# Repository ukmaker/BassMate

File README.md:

# BassMate

This is a simple drum machine and sequencer.

I want to be able to quickly create simple rhythm sequences to help me pratice electric bass, and was looking for something between a basic metronome and a full-fledged DAW.
The Drumbit online app (https://drumbit.app/) is pretty good, but having to point and click while playing an instrument is not tactile enough for me.
Accordingly, BassedMate (https://github.com/ukmaker/BassedMate) was born. This was the first iteration of the project, using a Teensy.

BassMate (this repo) is an evolution. I wanted to eliminate the VS1053 chip and I found the Electrosmith Daisy Seed (https://www.electro-smith.com/daisy/daisy)
which looked like it could do all the synthesis itself. I also found the MusicBoard project (https://github.com/julbouln/musicboard) which inspired me
to try to port to the Seed. This proved to be tricky, so I gave up (I'll try again one day!) and took a different path.

The UI of BassedMate felt a bit off, and when I came across the NavKey (https://coolcomponents.co.uk/products/i2c-navkey-7-function-joypad-black)
I thought I'd try something different. I also had an STM32F411 BlackPill (https://shop.pimoroni.com/products/stm32f411-blackpill-development-board?variant=39274213343315)
which has tons of memory and is really cheap.

So I remixed everything, sprinkled a new flavour of my GUI library (https://os.mbed.com/users/duncanFrance/code/SimpleGUI/) on the top and am happy with the result.

(https://youtu.be/watch?v=EM4BZbcfi_k)

# Installation
This is a PlatformIO project.

Clone this repository somewhere, then get the git submodules:
```
  git clone git@github.com:ukmaker/BassMate.git
  cd BassMate
  git submodule init
  git submodule update
```

Open the folder in PlatformIO, build and deploy as usual.

I have an ST-LINK V2 clone which I use to program Blue- and Black-pills. I throroughly
recommend it since with it you get to debug with single-step etc.

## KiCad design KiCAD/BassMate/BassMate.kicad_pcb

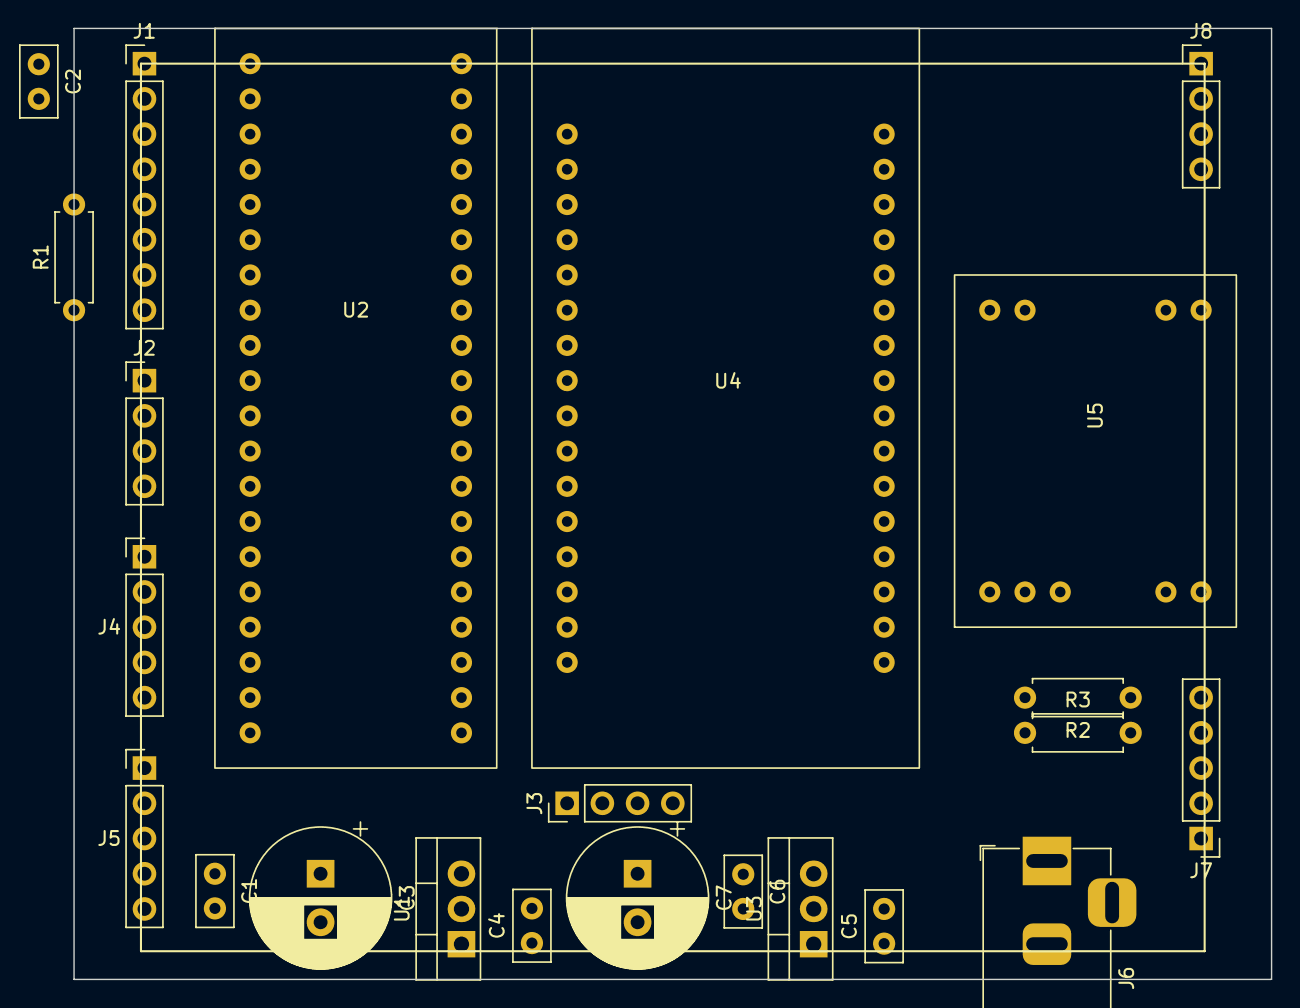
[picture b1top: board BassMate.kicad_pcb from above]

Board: 2 copper layers, 86.4 x 68.6 mm, 23 parts (0 on the bottom side), 36 nets, no tracks yet.

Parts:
C1, C2, C4, C5, C6: C; C_Disc_D5.0mm_W2.5mm_P2.50mm
C3, C7: C_Polarized; CP_Radial_D10.0mm_P3.50mm
J1: Conn_01x08; PinHeader_1x08_P2.54mm_Vertical
J2, J3, J8: Conn_01x04; PinHeader_1x04_P2.54mm_Vertical
J4, J5, J7: Conn_01x05; PinHeader_1x05_P2.54mm_Vertical
J6: Barrel_Jack; BarrelJack_Horizontal
R1: 3K9; R_Axial_DIN0207_L6.3mm_D2.5mm_P7.62mm_Horizontal
R2, R3: R; R_Axial_DIN0207_L6.3mm_D2.5mm_P7.62mm_Horizontal
U1: LM78M33; TO-220-3_Vertical
U2: BlackPill411; BlackPill_STM32F411
U3: LM7805; TO-220-3_Vertical
U4: Adafruit_VS1053_Module
U5: PAM8403_Module

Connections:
+3.3V: C2.2, J1.2, J4.1, R1.2, U2.18 (3V3)
+5V: C6.1, C7.1, U2.20 (5V), U3.3 (VO), U4.10 (VCC), U5.1 (+5V)
+9V: C4.1, C5.1, J6.1, U1.1 (VI), U3.1 (VI)
/INTNK: J4.5, U2.36 (B8)
/INTNT: J5.3, U2.37 (B9)
/SCL: J4.4, J5.2, U2.34 (B6)
/SDA: J4.3, J5.1, U2.35 (B7)
EL1: J2.2, U2.25 (A8)
EL2: J3.2, U2.7 (A1)
ER1: J2.1, U2.26 (A9)
ER2: J3.1, U2.6 (A0)
ES1: J2.3, U2.27 (A10)
ES2: J3.3, U2.4 (C15)
GND: C1.2, C2.1, C3.2, C4.2, C5.2, C6.2, C7.2, J1.1, J2.4, J3.4, J4.2, J5.5, J6.2, J7.5, R2.1, R3.1, U1.2 (GND), U2.19 (GND), U2.39 (GND), U3.2 (GND), U4.8 (DGND), U4.12 (GND), U4.13 (AGND), U4.14 (AGND), U4.20 (AGND), U5.2 (GND), U5.4 (AGND)
MISO: U2.12 (A6), U4.7 (MISO)
MOSI: U2.13 (A7), U4.6 (MOSI)
unnamed: C1.1, C3.1, J5.4, U1.3 (VO)
unnamed: J1.3, U2.22 (B13)
unnamed: J1.4, U2.24 (B15)
unnamed: J1.5, U2.32 (B4)
unnamed: J1.6, U2.30 (A15)
unnamed: J1.7, U2.21 (B12)
unnamed: J1.8, R1.1
unnamed: J7.1, U4.16 (ROUT)
unnamed: J7.2, R2.2, U5.5 (R_IN)
unnamed: J7.3, U4.15 (LOUT)
unnamed: J7.4, R3.2, U5.3 (L_IN)
unnamed: J8.1, U5.6 (L_OUT+)
unnamed: J8.2, U5.7 (L_OUT-)
unnamed: J8.3, U5.8 (R_OUT+)
unnamed: J8.4, U5.9 (R_OUT-)
unnamed: U2.14 (B0), U4.4 (XRST)
unnamed: U2.15 (B1), U4.3 (XCS)
unnamed: U2.16 (B2), U4.2 (XDCS)
SCK: U2.11 (A5), U4.5 (SCK)
TXD: U2.8 (A2), U4.31 (RX)

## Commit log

2022-06-14 Reimport after the great SSD meltdown
2022-06-14 Added NavKeyEventWrappers - no tests yet
2022-06-17 Refactored evvent wrapping to eliminate use of templating
2022-06-18 Simplified NavKeyEventWrapper support. Removed old event handling for now
2022-06-19 Much refactoring towards better separation of concerns
2022-06-20 More Controller/View split
2022-06-21 Improved handling of tabs and selects
2022-06-23 Started dialog for loading presets
2022-06-24 Improved various widgets
2022-06-25 Added Timer class to handle smple timeout callback
2022-06-25 It all works. Now for the tidy up
2022-06-26 Implement muting
2022-06-26 Deleted EventWrappers as not useful or general
2022-06-26 Removed old unused classes
2022-06-26 Made Rectangle properties protected
2022-06-26 Use simplegui namespace. Use unmodified Adafruit_GFX
2022-06-26 Use correct types
2022-06-26 Refactored DMA support
2022-06-26 Housekeeping and docs
2022-06-26 Cleanups
2022-06-28 Initialise the timer properly for encoder
2022-09-25 Pushing latest changes. Hope this works...
2022-10-30 Updated the 3D model for the box base
2022-10-31 Box updates
2022-12-15 The return of the AD5204 plus the two encoders
2022-12-15 Update schematic for AD5204. Better 3D case model.
2022-12-15 Removed old STLs and GCODE
2022-12-16 Started docs
2022-12-16 Docs
2022-12-17 Converted most libs to git sbmodules
2022-12-17 Updated README with build instructions
